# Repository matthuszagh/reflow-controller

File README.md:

A reflow oven controller, based on Henrik Forsten's project whose source code is found
[here](https://github.com/Ttl/reflow-controller). More in-depth documentation can be found in the
documentation subdirectory. The microcontroller code heavily leverages the [LUFA USB framework
code](http://www.fourwalledcubicle.com/LUFA.php).

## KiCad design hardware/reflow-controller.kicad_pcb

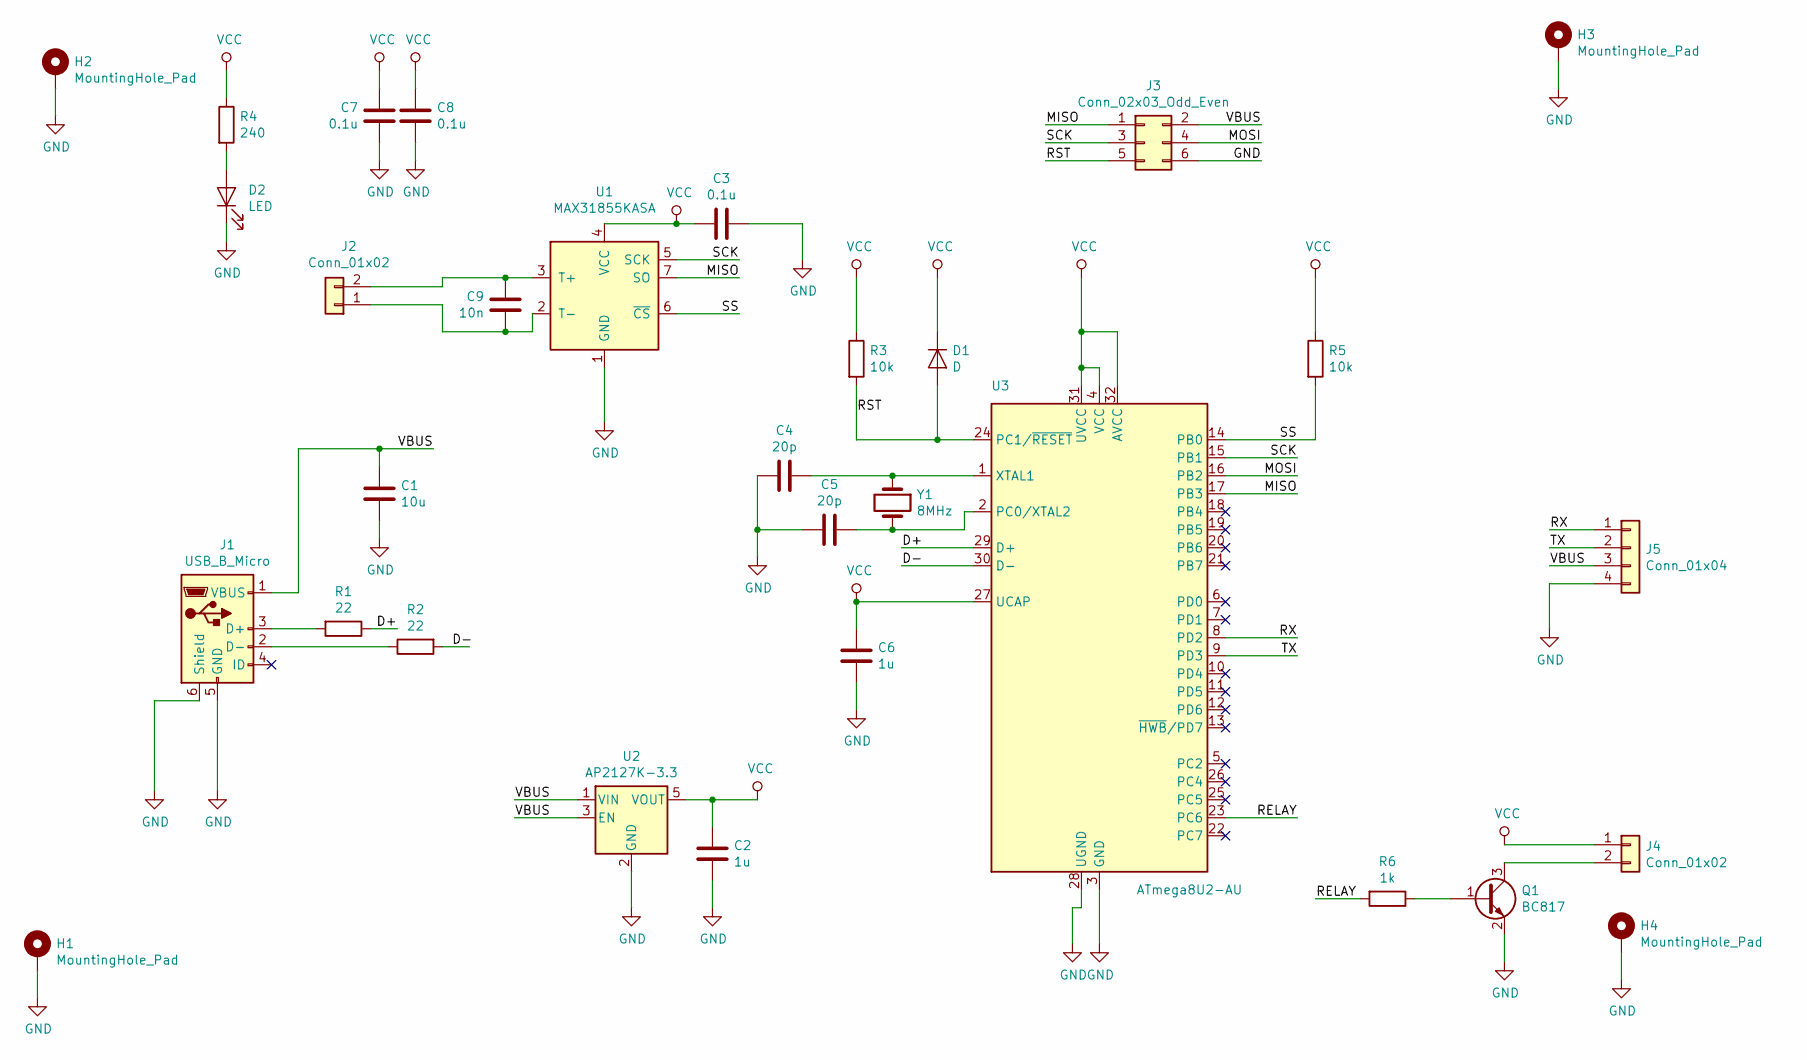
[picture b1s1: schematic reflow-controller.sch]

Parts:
C1: 10u; C_0603_1608Metric
C2, C6: 1u; C_0603_1608Metric
C3, C7, C8: 0.1u; C_0603_1608Metric
C4, C5: 20p; C_0603_1608Metric
C9: 10n; C_0603_1608Metric
D1: D; D_SOD-323
D2: LED; LED_0603_1608Metric
H1, H2, H3, H4: MountingHole_Pad; MountingHole_2.7mm_M2.5_Pad_Via
J1: USB_B_Micro; USB_Micro-B_Amphenol_10103594-0001LF_Horizontal
J2: Conn_01x02; TerminalBlock_Phoenix_MKDS-1,5-2_1x02_P5.00mm_Horizontal
J3: Conn_02x03_Odd_Even; PinHeader_2x03_P2.54mm_Vertical
J4: Conn_01x02; PinHeader_1x02_P2.54mm_Vertical
J5: Conn_01x04; PinHeader_1x04_P2.54mm_Vertical
Q1: BC817; SOT-23
R1, R2: 22; R_0603_1608Metric
R3, R5: 10k; R_0603_1608Metric
R4: 240; R_0603_1608Metric
R6: 1k; R_0603_1608Metric
U1: MAX31855KASA; SOIC-8_3.9x4.9mm_P1.27mm
U2: AP2127K-3.3; SOT-23-5
U3: ATmega8U2-AU; TQFP-32_7x7mm_P0.8mm
Y1: 8MHz; Crystal_SMD_HC49-SD

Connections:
/D+: R1.1, U3.29 (D+)
/D-: R2.2, U3.30 (D-)
/MISO: J3.1, U1.7 (SO), U3.17 (PB3)
/MOSI: J3.4, U3.16 (PB2)
/RELAY: R6.2, U3.23 (PC6)
/RST: D1.2 (A), J3.5, R3.2, U3.24 (PC1/~RESET)
/RX: J5.1, U3.8 (PD2)
/SCK: J3.3, U1.5 (SCK), U3.15 (PB1)
/SS: R5.2, U1.6 (~CS~), U3.14 (PB0)
/TX: J5.2, U3.9 (PD3)
/VBUS: C1.1, J1.1 (VBUS), J3.2, J5.3, U2.1 (VIN), U2.3 (EN)
GND: C1.2, C2.2, C3.1, C4.2, C5.2, C6.2, C7.2, C8.2, D2.1 (K), H1.1, H2.1, H3.1, H4.1, J1.5 (GND), J1.6 (Shield), J3.6, J5.4, Q1.2 (E), U1.1 (GND), U2.2 (GND), U3.3 (GND), U3.28 (UGND)
unnamed: C4.1, U3.1 (XTAL1), Y1.1
unnamed: C5.1, U3.2 (PC0/XTAL2), Y1.2
unnamed: C9.1, J2.2, U1.3 (T+)
unnamed: C9.2, J2.1, U1.2 (T-)
unnamed: D2.2 (A), R4.2
unnamed: J1.2 (D-), R2.1
unnamed: J1.3 (D+), R1.2
unnamed: J4.2, Q1.3 (C)
unnamed: Q1.1 (B), R6.1
VCC: C2.1, C3.2, C6.1, C7.1, C8.1, D1.1 (K), J4.1, R3.1, R4.1, R5.1, U1.4 (VCC), U2.5 (VOUT), U3.4 (VCC), U3.27 (UCAP), U3.31 (UVCC), U3.32 (AVCC)

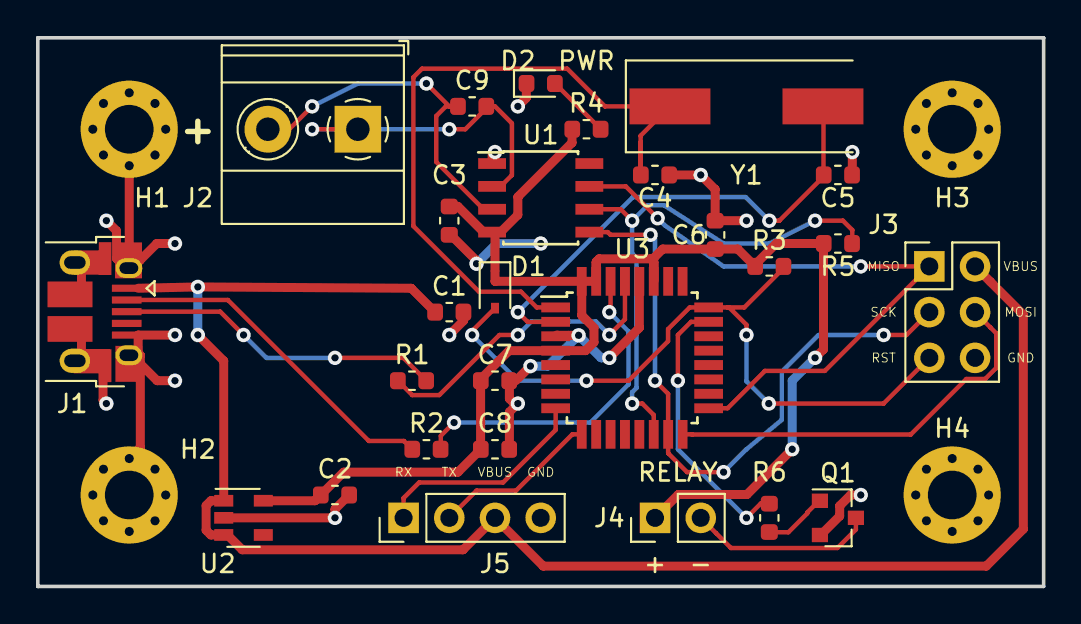
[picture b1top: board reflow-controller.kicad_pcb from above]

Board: 2 copper layers, 55.9 x 30.5 mm, 31 parts (0 on the bottom side), 22 nets.

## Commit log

2018-06-22 Updated Makefile.
2018-06-27 Kicad version of design.
2018-06-28 PCB passes DRC.
2018-06-29 PCB is complete and has been sent to fab.
2018-07-25 Updated microcontroller code.
2018-07-25 PCB design complete and updated microcontroller code.
2018-08-08 Working version with new reflow profile.
2018-10-04 Fixed power supply when programmed by ISP, added mounting holes, replaced mini USB connector with micro connector.
2018-11-02 Fixed minimum values for solder mask clearance and width.
2018-11-04 Adjusted solder mask relief and rewrote PC code in C++.
2018-11-06 Added documentation.
2018-11-07 Improved performance of pc code.
2018-12-18 Improved solder mask dam size.
2019-01-03 Bom generation improvements.
2019-01-05 Improved pc software and added MFN to schematic for USB receptacle.
2019-02-05 Improved pc code.
2019-02-05 Improved mcu and pc code.
2019-09-23 Fix pc code and create reproducible Nix environment
